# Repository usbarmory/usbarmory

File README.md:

Introduction
============

The USB armory is an open source hardware design, implementing a compact secure
computer.

This repository is aimed towards developers, if you wish to purchase a USB
armory board please see the [ordering information](https://github.com/usbarmory/usbarmory/wiki/Ordering-information).

Authors
=======

Andrea Barisani  
andrea@inversepath.com  

Andrej Rosano  
andrej@inversepath.com  

Daniele Bianco  
daniele@inversepath.com  

Documentation
=============

The main documentation can be found on the
[project wiki](https://github.com/usbarmory/usbarmory/wiki).

Board models
============

* [USB armory Mk II LAN](https://github.com/usbarmory/usbarmory/wiki/Mk-II-LAN)

* [USB armory Mk II](https://github.com/usbarmory/usbarmory/wiki/Mk-II-Introduction)

* USB armory Mk I

License
=======

USB armory | https://github.com/usbarmory/usbarmory  
Copyright (c) The USB armory authors

This is an open hardware design licensed under the terms of the CERN Open
Hardware Licence, see board revisions for applicable versions.

This source is distributed WITHOUT ANY EXPRESS OR IMPLIED WARRANTY, INCLUDING
OF MERCHANTABILITY, SATISFACTORY QUALITY AND FITNESS FOR A PARTICULAR PURPOSE.

Please see LICENSE files in each source subdirectory for applicable conditions.

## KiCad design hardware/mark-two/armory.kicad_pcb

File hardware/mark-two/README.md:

Introduction
============

The USB armory is an open source hardware design, implementing a flash drive
sized computer.

This repository is aimed towards developers, if you wish to purchase a USB
armory board please see the [ordering information](https://github.com/usbarmory/usbarmory/wiki/Ordering-information).

Authors
=======

Andrea Barisani  
andrea@inversepath.com  

Andrej Rosano  
andrej@inversepath.com  

Daniele Bianco  
daniele@inversepath.com  

Documentation
=============

The main documentation can be found on the
[project wiki](https://github.com/usbarmory/usbarmory/wiki).

Revision information
====================

This directory contains the hardware design for the USB armory Mk II rev. δ.

Current schematics and layout files have been designed in KiCad 10.0.8.

PCB Information
===============

6 layers, 0.8mm thickness  
Outer layers 0.5 oz base copper foil  
Inner layers   1 oz base copper foil  
width (X) 65.6 mm, height (Y) 19.5 mm  
Electroless Nickel Immersion Gold (ENIG) surface finish  
Black resist, white component legend

Layers
------

Order and type of copper layers:  
  TOP:         signal, front components  
  SIGNAL 1:    signal  
  GND POWER 1: ground and power plane  
  GND POWER 2: ground and power plane  
  SIGNAL 2:    signal  
  BOTTOM:      signal, back components  

| Layer | Description               |  Thickness (in um)  |
|:-----:|---------------------------|:-------------------:|
|       | LPI mask                  |   15                |
|       | ENIG plating              |   18                |
|   1   | copper                    |   30                |
|       | prepreg, 2 x PP 106       |  121                |
|   2   | copper                    |   17                |
|       | core, FR4 17/17           |  125                |
|   3   | copper                    |   17                |
|       | prepreg, 2 x PP 106       |  116                |
|   4   | copper                    |   17                |
|       | core, FR4 17/17           |  125                |
|   5   | copper                    |   17                |
|       | prepreg, 2 x PP 106       |  121                |
|   6   | copper                    |   30                |
|       | ENIG plating              |   18                |
|       | LPI mask                  |   15                |

Material: Isola PCL370-HR
Total thickness: 0.8 mm

DRC information
---------------

Minimum track width:            0.100 mm  
Minimum via diameter:           0.406 mm  
Outer layer track width:        0.100 mm  
Outer layer isolation distance: 0.100 mm  
Outer layer annular ring:       0.075 mm  
Inner layer track width:        0.100 mm  
Inner layer isolation distance: 0.100 mm  
Inner layer annular ring:       0.075 mm  
Smallest final hole (plated):   0.150 mm

Regulatory compliance & handling
================================

The USB armory board is an open system design, which does not include a
shielded enclosure. This may cause interference to other electrical or
electronic devices in close proximity. In a domestic environment, this product
may cause radio interference in which case the user may be required to take
adequate measures. In addition, this board should not be used near any medical
equipment or RF devices.

The board is sensitive to Electrostatic discharge (ESD). Hold the board only by
its edges. After removing the board from its box, place it on a grounded,
static-free surface.

The board can become hot, like any fan-less design, during continuous high CPU
loads, mind its temperature while handling it.

* [Compliance information](https://github.com/usbarmory/usbarmory/wiki/Compliance-information)

License
=======

USB armory | https://github.com/usbarmory/usbarmory  
Copyright (c) The USB armory authors

This source describes Open Hardware and is licensed under the CERN-OHL-S v2.

You may redistribute and modify this source and make products using it under
the terms of the CERN-OHL-S v2 (https://ohwr.org/cern_ohl_s_v2.txt).

This source is distributed WITHOUT ANY EXPRESS OR IMPLIED WARRANTY, INCLUDING
OF MERCHANTABILITY, SATISFACTORY QUALITY AND FITNESS FOR A PARTICULAR PURPOSE.
Please see the CERN-OHL-S v2 for applicable conditions.

As per CERN-OHL-S v2 section 4, should You produce hardware based on this
source, You must where practicable maintain the Source Location visible on the
external case of the USB armory or other products you make using this source.

The following exceptions apply:

- `../lib.snapeda`: all files in this directory are imported or modified
  from SnapEDA symbols and footprints, therefore the license at
  https://www.snapeda.com/about/FAQ/#license applies.

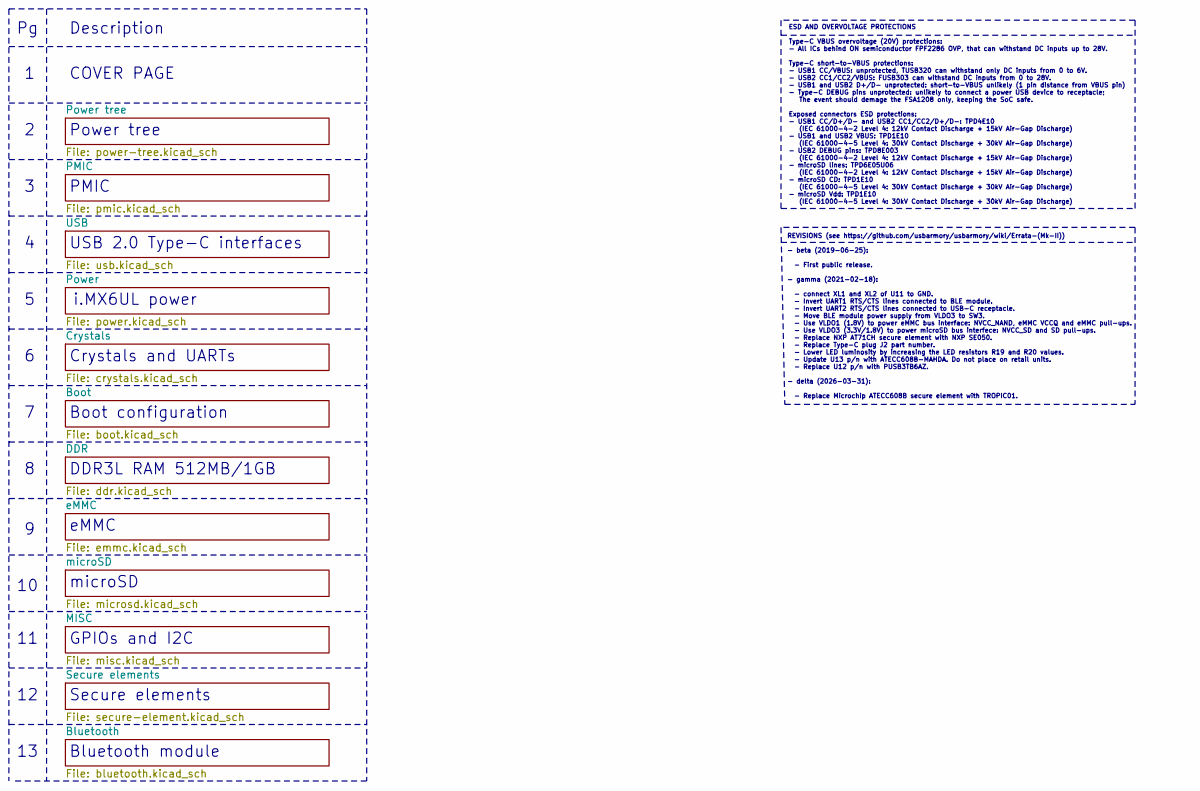
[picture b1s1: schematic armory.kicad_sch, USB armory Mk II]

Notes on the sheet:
Crystals and UARTs
ESD AND OVERVOLTAGE PROTECTIONS Type-C VBUS overvoltage (20V) protections: - All ICs behind ON semiconductor FPF2286 OVP, that can withstand DC inputs up to 28V. Type-C short-to-VBUS protections: - USB1 CC/VBUS: unprotected, TUSB320 can withstand only DC inputs from 0 to 6V. - USB2 CC1/CC2/VBUS: FU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
Power tree
PMIC
Boot configuration
COVER PAGE
microSD
i.MX6UL power
USB 2.0 Type-C interfaces
GPIOs and I2C
eMMC
REVISIONS (see https://github.com/usbarmory/usbarmory/wiki/Errata-(Mk-II)) - beta (2019-06-25): - First public release. - gamma (2021-02-18): - connect XL1 and XL2 of U11 to GND. - Invert UART1 RTS/CTS lines connected to BLE module. - Invert UART2 RTS/CTS lines connected to USB-C receptacle. - Move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
DDR3L RAM 512MB/1GB
Bluetooth module
Description
Secure elements

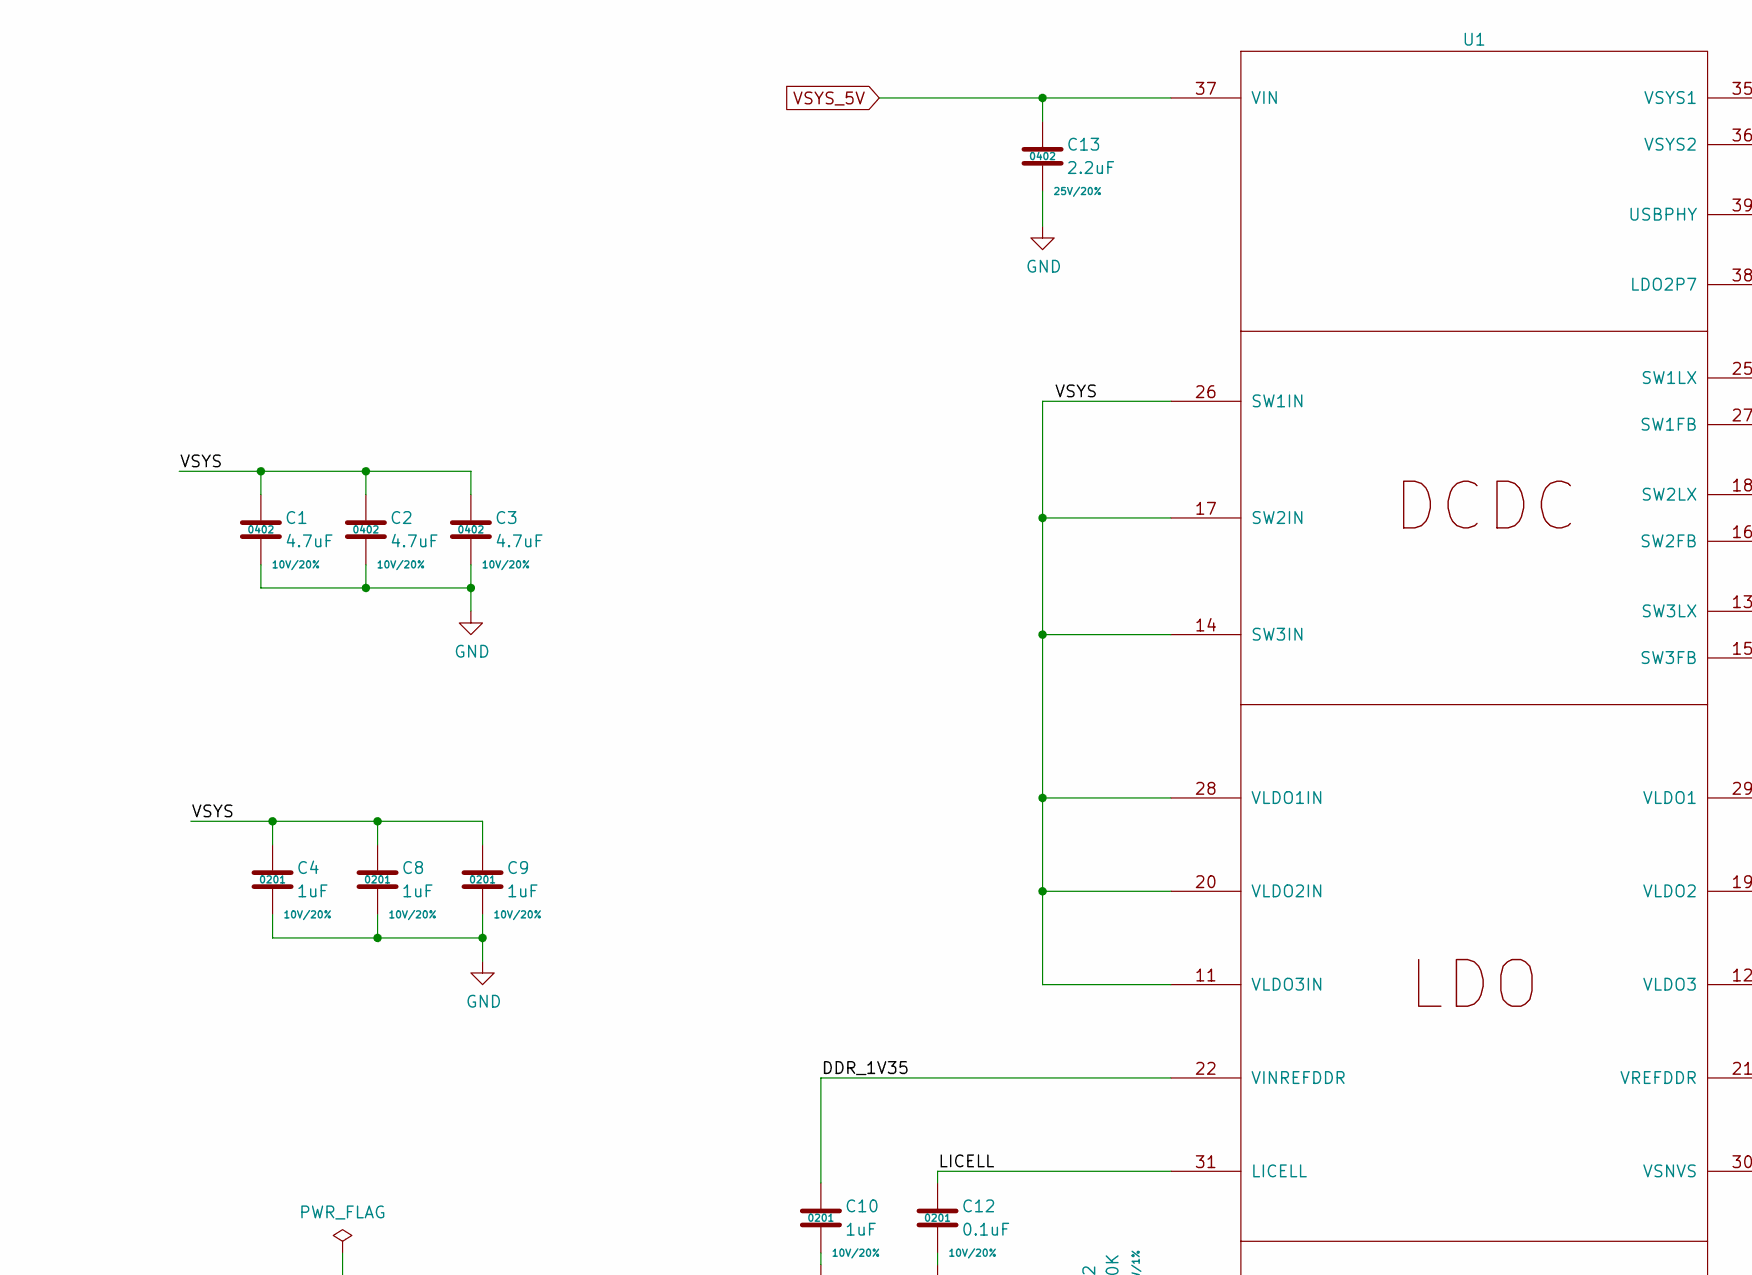
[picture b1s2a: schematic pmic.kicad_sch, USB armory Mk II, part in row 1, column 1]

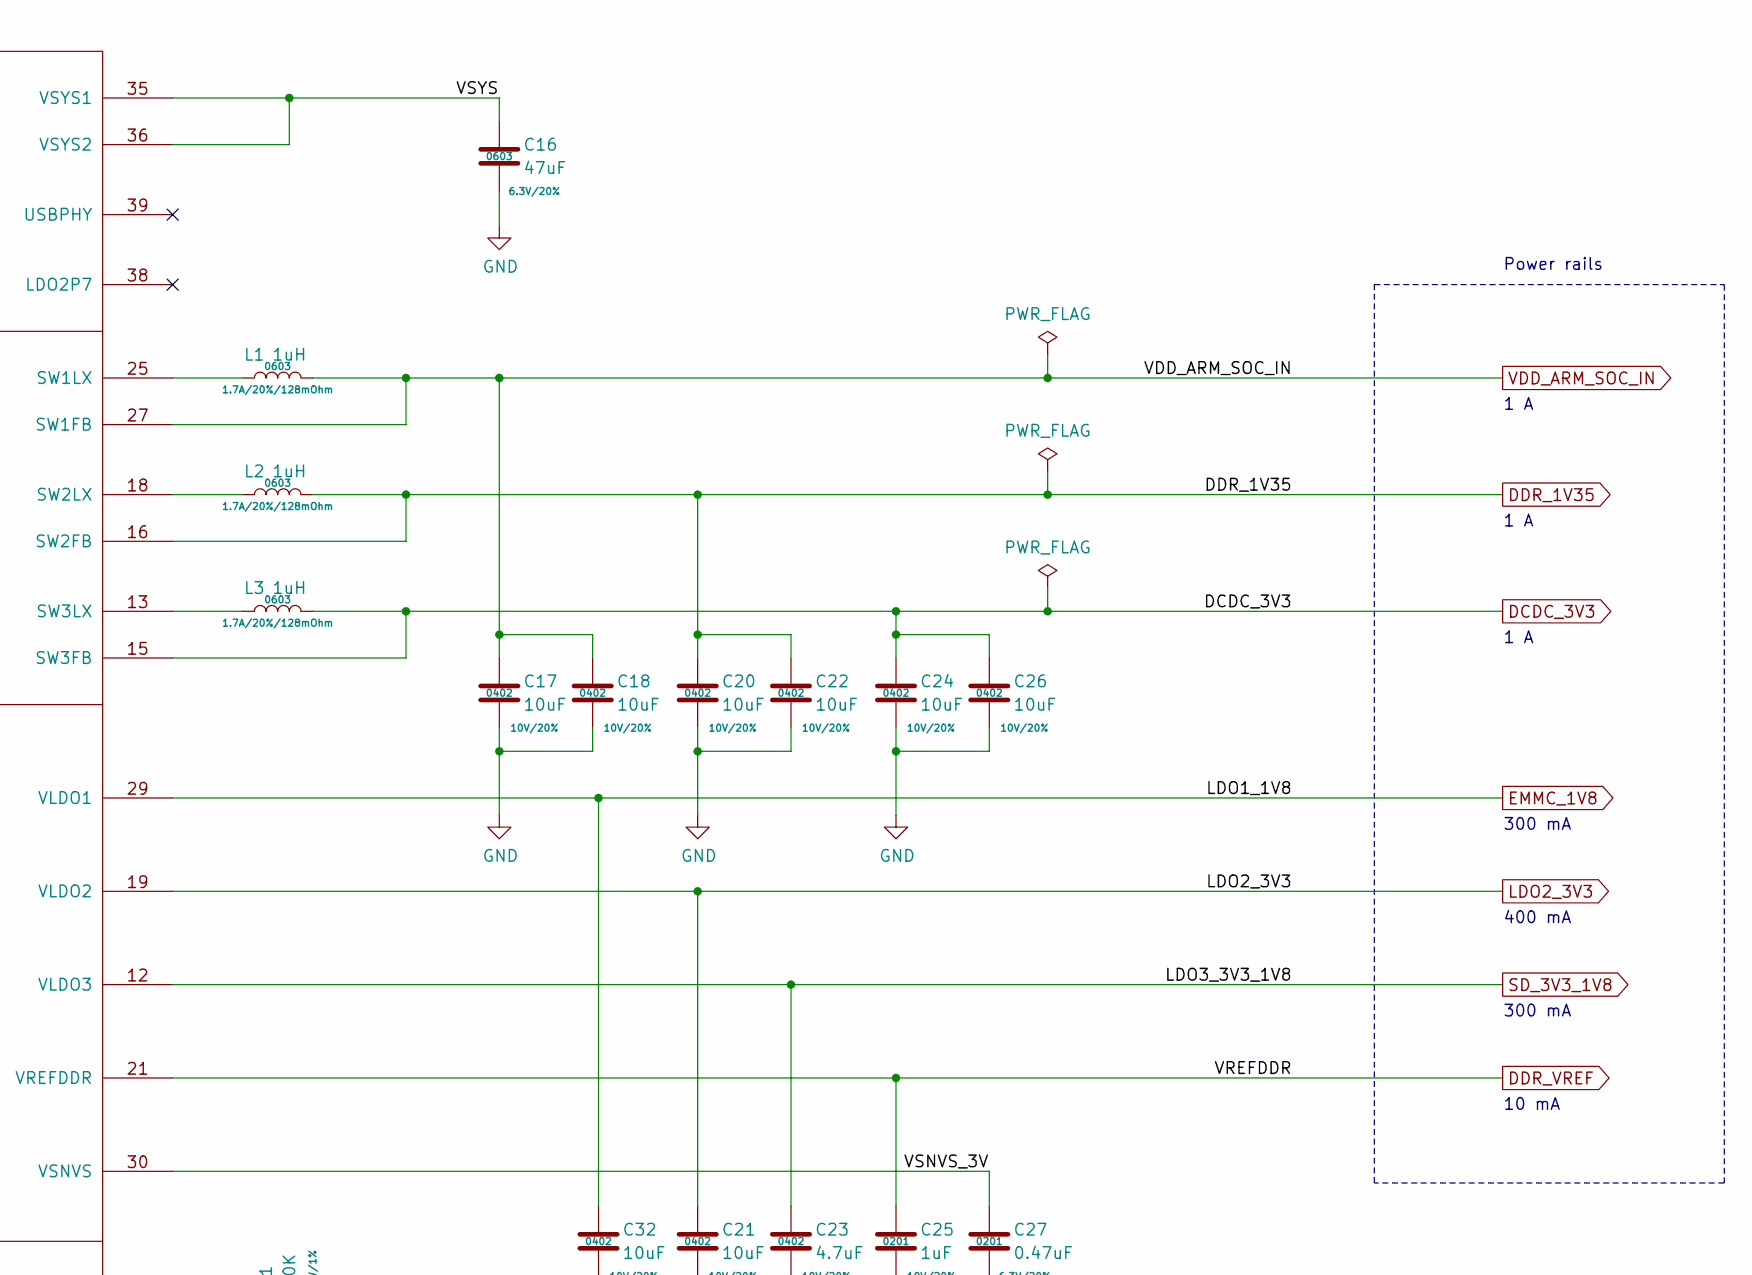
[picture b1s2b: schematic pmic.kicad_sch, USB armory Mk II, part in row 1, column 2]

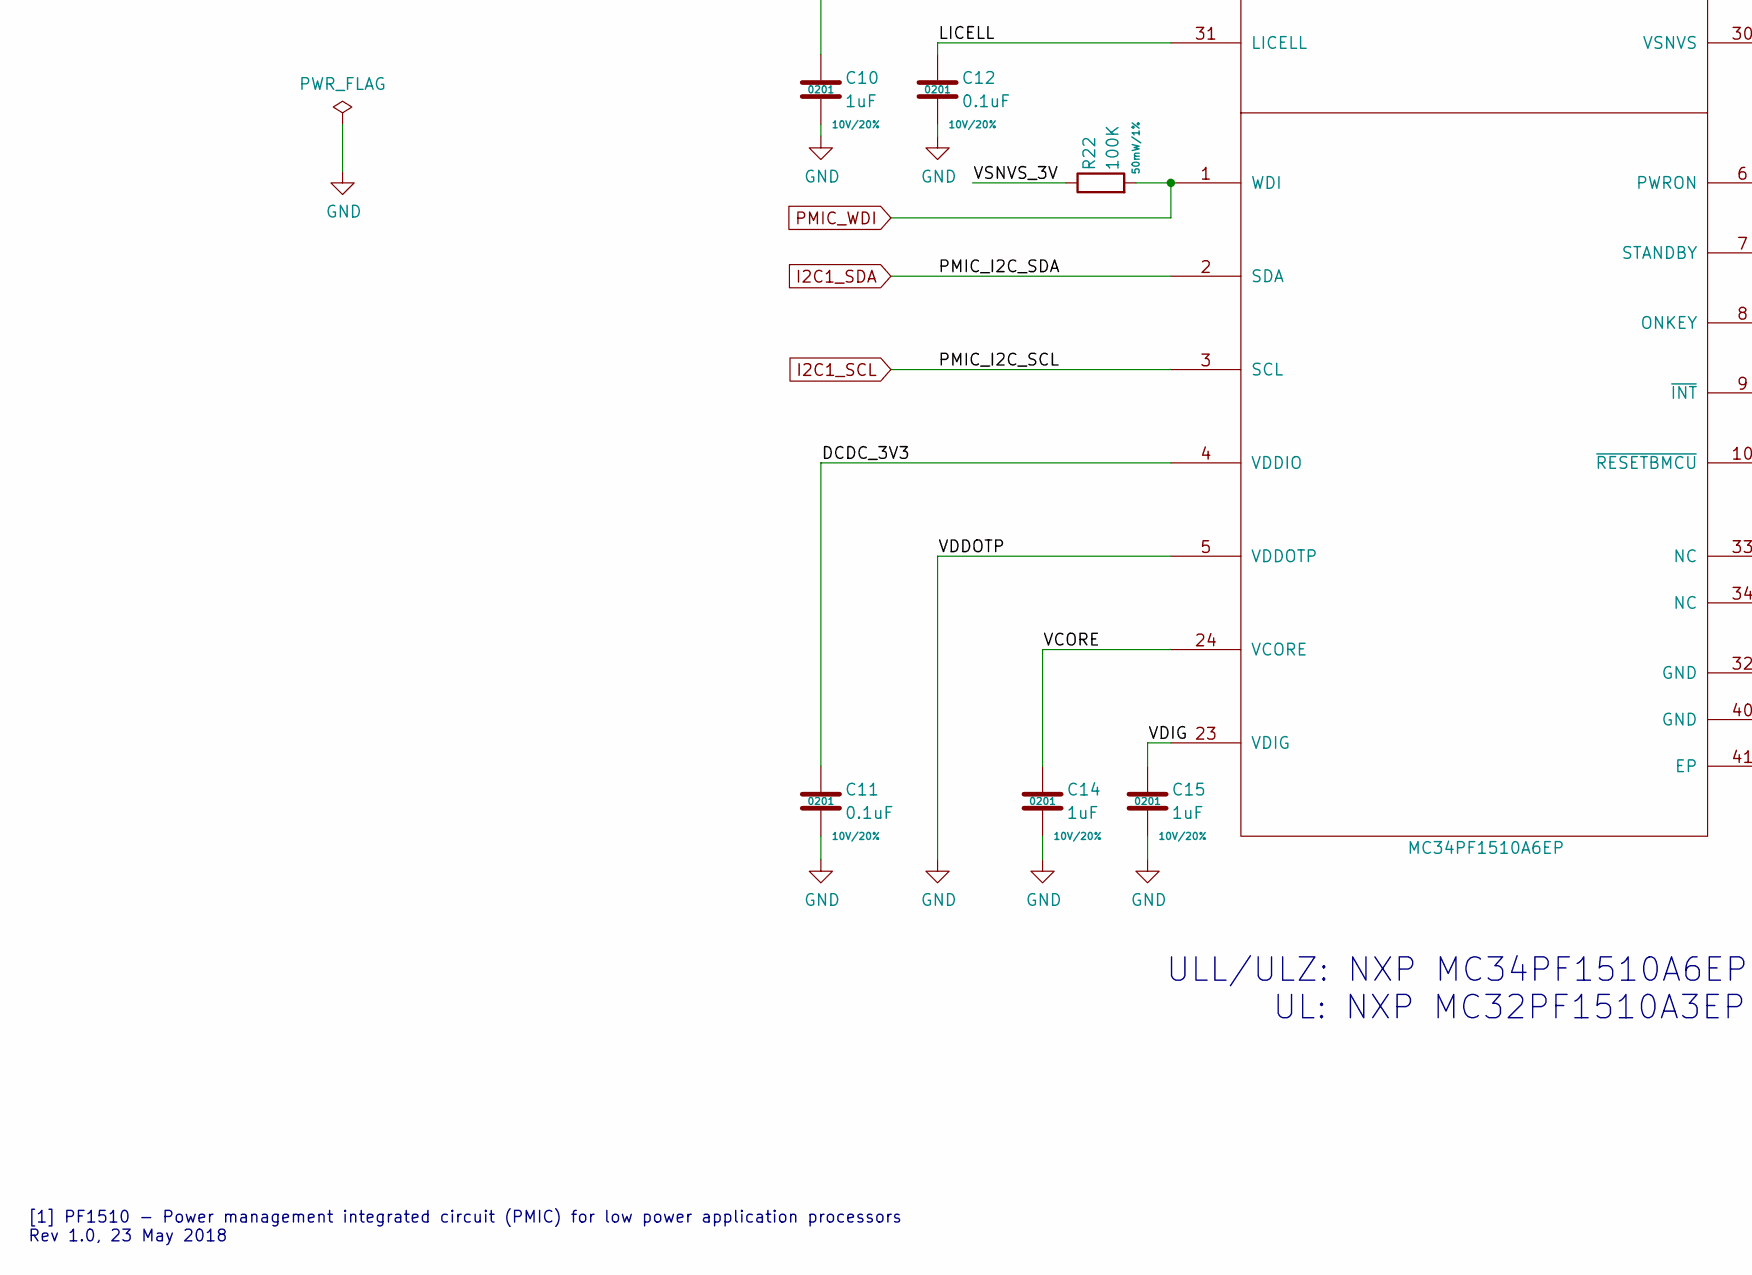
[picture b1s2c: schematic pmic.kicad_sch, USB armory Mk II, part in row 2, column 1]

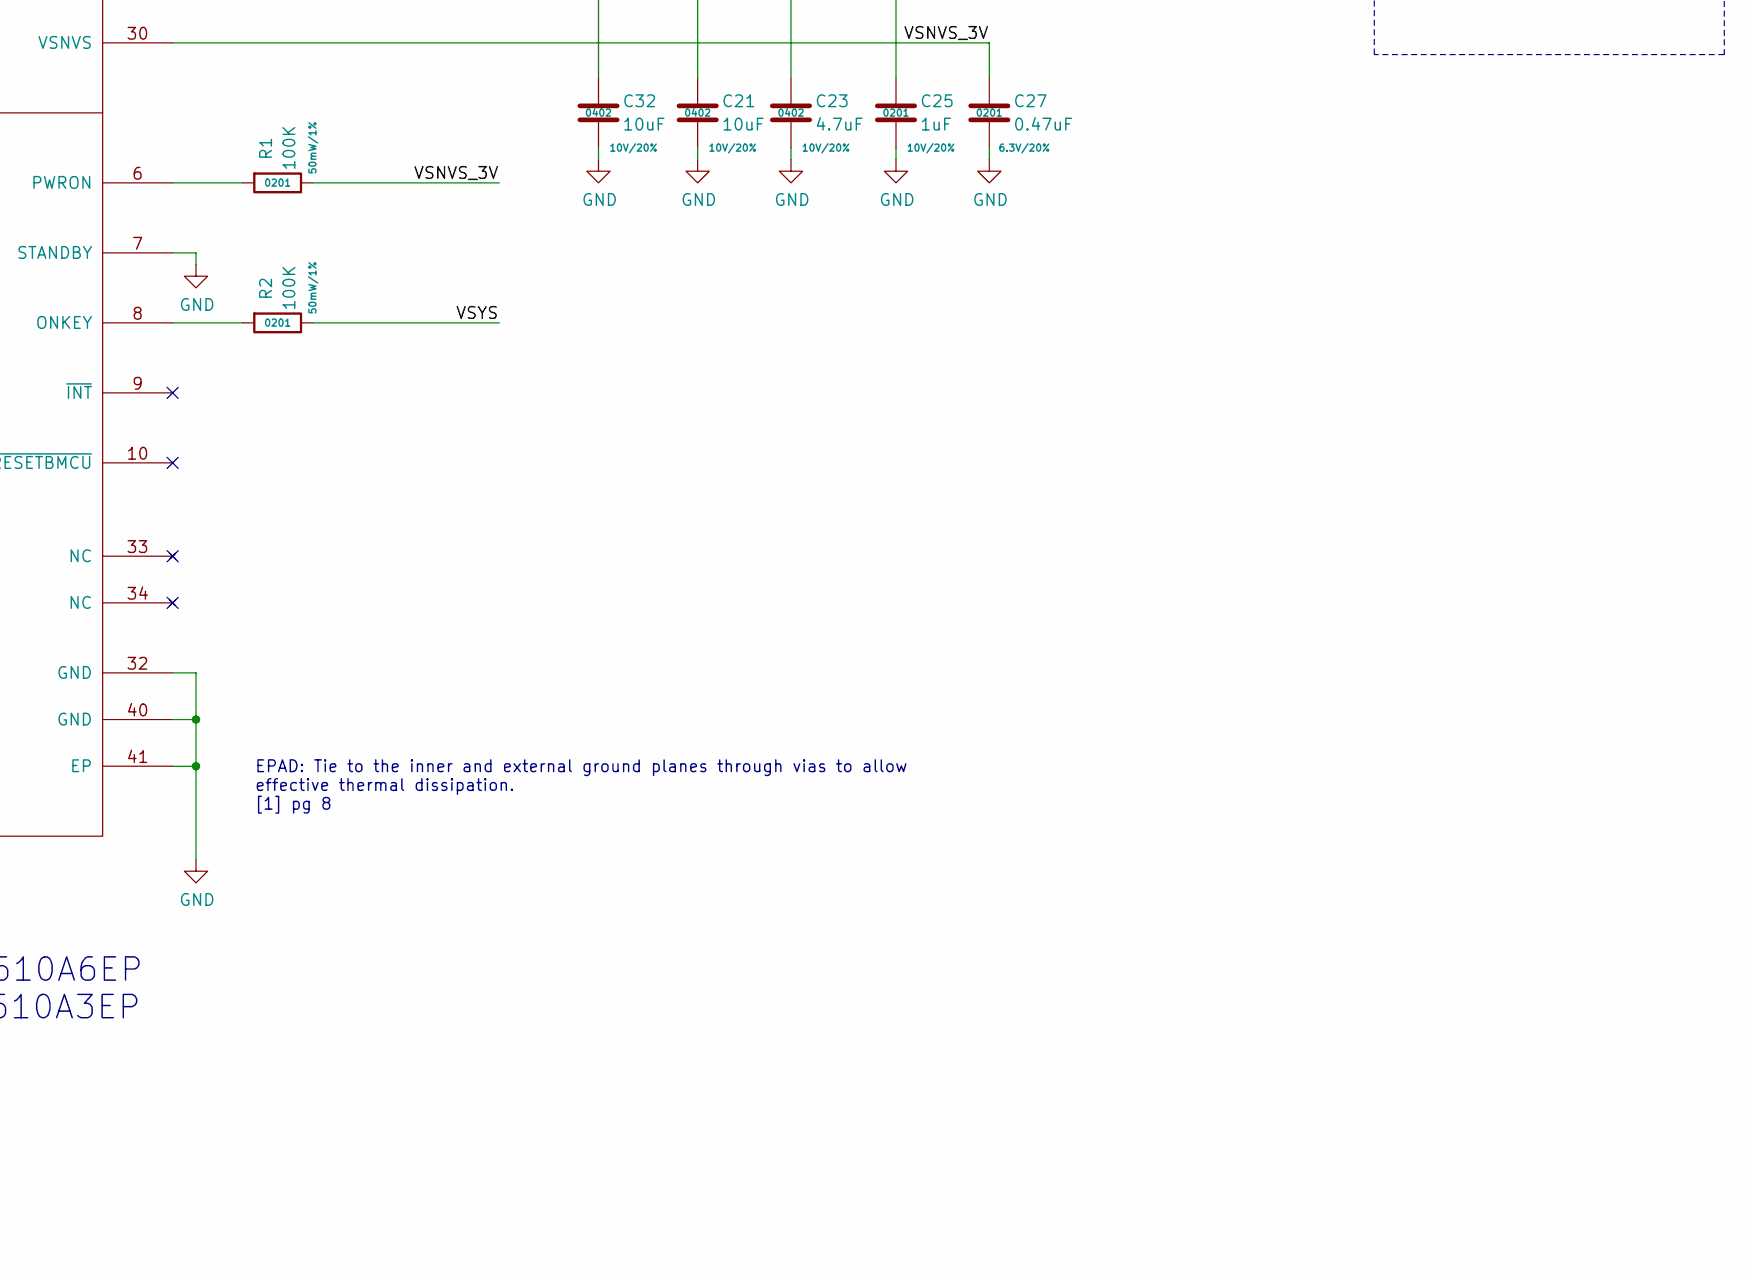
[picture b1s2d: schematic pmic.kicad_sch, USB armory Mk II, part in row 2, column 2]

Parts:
C1, C2, C3, C23: 4.7uF; SM0402; Rating 10V/20%; Mfg PN ZRB15XR61A475ME01D
C4, C8, C9, C10, C14, C15, C25: 1uF; SM0201; Rating 10V/20%; Mfg PN GRM033R61A105ME15D
C11, C12: 0.1uF; SM0201; Rating 10V/20%; Mfg PN GRM033R61A104ME15D
C13: 2.2uF; SM0402; Rating 25V/20%; Mfg PN GRM155R61E225ME15D
C16: 47uF; SM0603; Rating 6.3V/20%; Mfg PN GRM188R60J476ME15D
C17, C18, C20, C21, C22, C24, C26, C32: 10uF; SM0402; Rating 10V/20%; Mfg PN CL05A106MP8NUB8
C27: 0.47uF; SM0201; Rating 6.3V/20%; Mfg PN GRM033R60J474ME90D
L1, L2, L3: 1uH; SM0603; Rating 1.7A/20%/128mOhm; Mfg PN DFE18SAN1R0MG0L
R1, R2, R22: 100K; SM0201; Rating 50mW/1%; Mfg PN CRCW0201100KJNED
U1: MC34PF1510A6EP; SOT1369-4; Mfg PN MC34PF1510A6EP

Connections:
/PMIC/LICELL: C12.1, U1.31 (LICELL)
/PMIC/VCORE: C14.1, U1.24 (VCORE)
/PMIC/VDIG: C15.1, U1.23 (VDIG)
/PMIC/VSNVS_3V: C27.1, R1.1, R22.1, U1.30 (VSNVS)
/PMIC/VSYS: C1.1, C2.1, C3.1, C4.1, C8.1, C9.1, C16.1, R2.1, U1.11 (VLDO3IN), U1.14 (SW3IN), U1.17 (SW2IN), U1.20 (VLDO2IN), U1.26 (SW1IN), U1.28 (VLDO1IN), U1.35 (VSYS1), U1.36 (VSYS2)
DCDC_3V3: C11.1, C24.1, C26.1, L3.2, U1.4 (VDDIO), U1.15 (SW3FB); also elsewhere on the board
DDR_1V35: C10.1, C20.1, C22.1, L2.2, U1.16 (SW2FB), U1.22 (VINREFDDR); also elsewhere on the board
DDR_VREF: C25.1, U1.21 (VREFDDR); also elsewhere on the board
EMMC_1V8: C32.1, U1.29 (VLDO1); also elsewhere on the board
GND: C1.2, C2.2, C3.2, C4.2, C8.2, C9.2, C10.2, C11.2, C12.2, C13.2, C14.2, C15.2, C16.2, C17.2, C18.2, C20.2, C21.2, C22.2, C23.2, C24.2, C25.2, C26.2, C27.2, C32.2, U1.5 (VDDOTP), U1.7 (STANDBY), U1.32 (GND), U1.40 (GND), U1.41 (EP); also elsewhere on the board
I2C1_SCL: U1.3 (SCL); also elsewhere on the board
I2C1_SDA: U1.2 (SDA); also elsewhere on the board
LDO2_3V3: C21.1, U1.19 (VLDO2); also elsewhere on the board
unnamed: R2.2, U1.8 (ONKEY)
unnamed: R1.2, U1.6 (PWRON)
unnamed: L1.1, U1.25 (SW1LX)
unnamed: L2.1, U1.18 (SW2LX)
unnamed: L3.1, U1.13 (SW3LX)
PMIC_WDI: R22.2, U1.1 (WDI); also elsewhere on the board
SD_3V3_1V8: C23.1, U1.12 (VLDO3); also elsewhere on the board
VDD_ARM_SOC_IN: C17.1, C18.1, L1.2, U1.27 (SW1FB); also elsewhere on the board
VSYS_5V: C13.1, U1.37 (VIN); also elsewhere on the board

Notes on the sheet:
300 mA
EPAD: Tie to the inner and external ground planes through vias to allow effective thermal dissipation. [1] pg 8
10 mA
ULL/ULZ: NXP MC34PF1510A6EP UL: NXP MC32PF1510A3EP
1 A
[1] PF1510 - Power management integrated circuit (PMIC) for low power application processors Rev 1.0, 23 May 2018
Power rails
400 mA

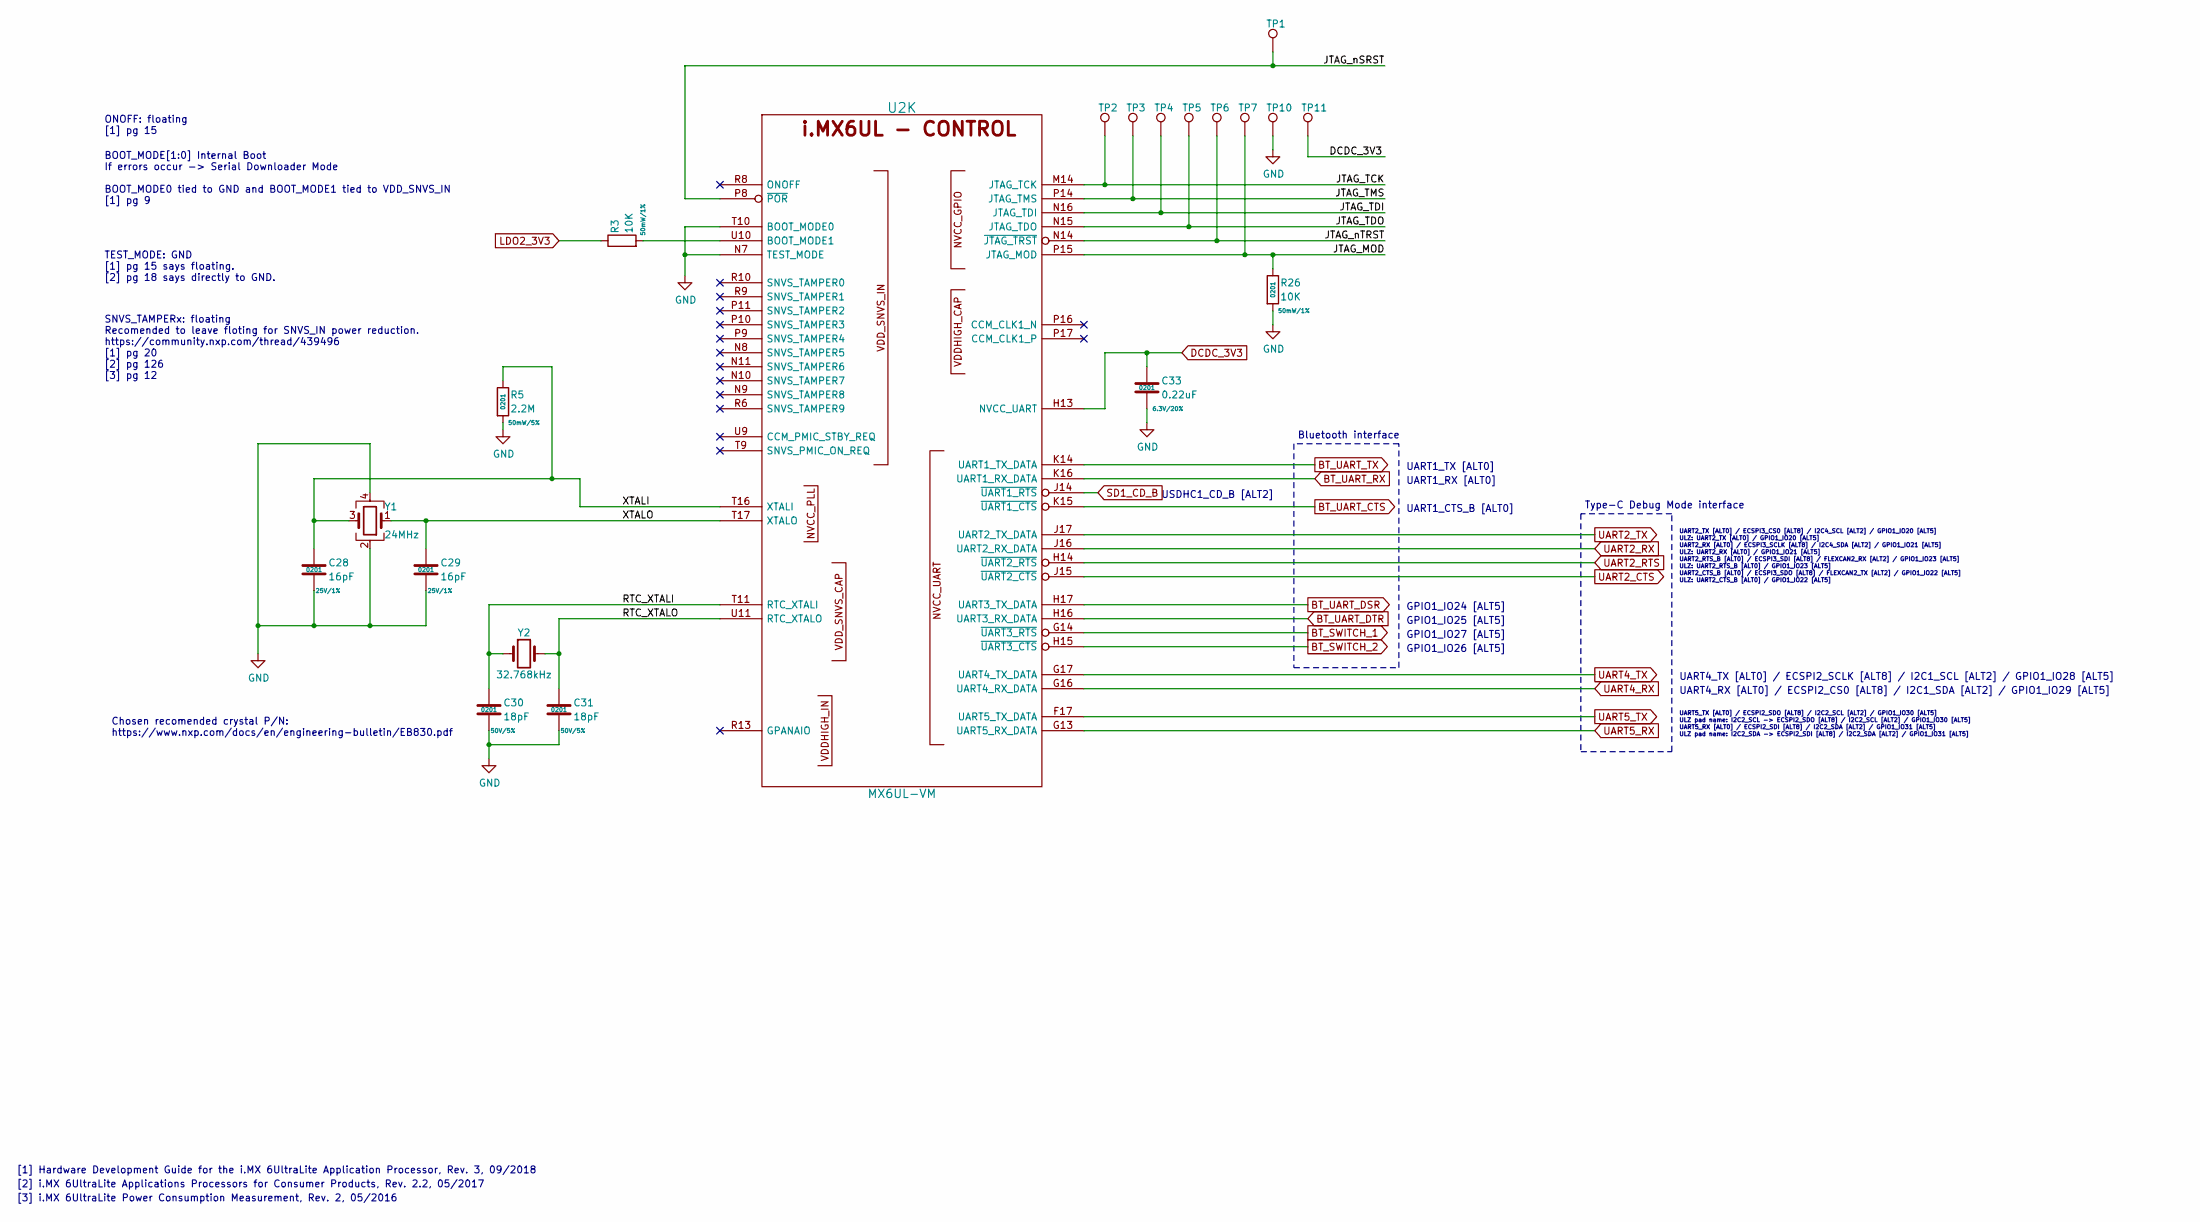
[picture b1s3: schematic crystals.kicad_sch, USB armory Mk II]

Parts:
C28, C29: 16pF; SM0201; Rating 25V/1%; Mfg PN CBR02C160F3GAC
C30, C31: 18pF; SM0201; Rating 50V/5%; Mfg PN GRM0335C1H180JA01D
C33: 0.22uF; SM0201; Rating 6.3V/20%; Mfg PN GRM033R60J224ME15D
R3, R26: 10K; SM0201; Rating 50mW/1%; Mfg PN CRCW020110K0JNED
R5: 2.2M; SM0201; Rating 50mW/5%; Mfg PN RC0201JR-072M2L
TP1, TP2, TP3, TP4, TP5, TP6, TP7, TP10, TP11: TestPoint; TP
U2: MX6UL-VM; SOT1534-2; Mfg PN MCIMX6Z0DVM09AB
Y1: 24MHz; TSX-3225; Mfg PN TSX-3225 24.0000MF15X-AC3
Y2: 32.768kHz; CM7V-T1A; Mfg PN CM7V-T1A-32.768kHz-12.5pF-20PPM-TA-QC

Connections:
/Crystals/JTAG_MOD: R26.1, TP7.1 (1_1), U2.P15 (JTAG_MOD)
/Crystals/JTAG_TCK: TP2.1 (1_1), U2.M14 (JTAG_TCK)
/Crystals/JTAG_TDI: TP4.1 (1_1), U2.N16 (JTAG_TDI)
/Crystals/JTAG_TDO: TP5.1 (1_1), U2.N15 (JTAG_TDO)
/Crystals/JTAG_TMS: TP3.1 (1_1), U2.P14 (JTAG_TMS)
/Crystals/JTAG_nSRST: TP1.1 (1_1), U2.P8 (~POR)
/Crystals/JTAG_nTRST: TP6.1 (1_1), U2.N14 (~JTAG_TRST)
/Crystals/RTC_XTALI: C30.1, U2.T11 (RTC_XTALI), Y2.1
/Crystals/RTC_XTALO: C31.1, U2.U11 (RTC_XTALO), Y2.2
/Crystals/XTALI: C28.1, R5.1, U2.T16 (XTALI), Y1.3
/Crystals/XTALO: C29.1, U2.T17 (XTALO), Y1.1
BT_SWITCH_1: U2.G14 (~UART3_RTS); also elsewhere on the board
BT_SWITCH_2: U2.H15 (~UART3_CTS); also elsewhere on the board
BT_UART_CTS: U2.K15 (~UART1_CTS); also elsewhere on the board
BT_UART_DSR: U2.H17 (UART3_TX_DATA); also elsewhere on the board
BT_UART_DTR: U2.H16 (UART3_RX_DATA); also elsewhere on the board
BT_UART_RX: U2.K16 (UART1_RX_DATA); also elsewhere on the board
BT_UART_TX: U2.K14 (UART1_TX_DATA); also elsewhere on the board
DCDC_3V3: C33.1, TP11.1 (1_1), U2.H13 (NVCC_UART); also elsewhere on the board
GND: C28.2, C29.2, C30.2, C31.2, C33.2, R5.2, R26.2, TP10.1 (1_1), U2.N7 (TEST_MODE), U2.T10 (BOOT_MODE0), Y1.2, Y1.4; also elsewhere on the board
LDO2_3V3: R3.1; also elsewhere on the board
unnamed: R3.2, U2.U10 (BOOT_MODE1)
SD1_CD_B: U2.J14 (~UART1_RTS); also elsewhere on the board
UART2_CTS: U2.J15 (~UART2_CTS); also elsewhere on the board
UART2_RTS: U2.H14 (~UART2_RTS); also elsewhere on the board
UART2_RX: U2.J16 (UART2_RX_DATA); also elsewhere on the board
UART2_TX: U2.J17 (UART2_TX_DATA); also elsewhere on the board
UART4_RX: U2.G16 (UART4_RX_DATA); also elsewhere on the board
UART4_TX: U2.G17 (UART4_TX_DATA); also elsewhere on the board
UART5_RX: U2.G13 (UART5_RX_DATA); also elsewhere on the board
UART5_TX: U2.F17 (UART5_TX_DATA); also elsewhere on the board

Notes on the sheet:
UART1_RX [ALT0]
UART4_RX [ALT0] / ECSPI2_CS0 [ALT8] / I2C1_SDA [ALT2] / GPIO1_IO29 [ALT5]
UART4_TX [ALT0] / ECSPI2_SCLK [ALT8] / I2C1_SCL [ALT2] / GPIO1_IO28 [ALT5]
BOOT_MODE[1:0] Internal Boot If errors occur -> Serial Downloader Mode BOOT_MODE0 tied to GND and BOOT_MODE1 tied to VDD_SNVS_IN [1] pg 9
GPIO1_IO26 [ALT5]
UART2_RX [ALT0] / ECSPI3_SCLK [ALT8] / I2C4_SDA [ALT2] / GPIO1_IO21 [ALT5]
UART5_RX [ALT0] / ECSPI2_SDI [ALT8] / I2C2_SDA [ALT2] / GPIO1_IO31 [ALT5]
ULZ: UART2_RX [ALT0] / GPIO1_IO21 [ALT5]
GPIO1_IO25 [ALT5]
UART5_TX [ALT0] / ECSPI2_SDO [ALT8] / I2C2_SCL [ALT2] / GPIO1_IO30 [ALT5]
GPIO1_IO24 [ALT5]
ULZ: UART2_CTS_B [ALT0] / GPIO1_IO22 [ALT5]
USDHC1_CD_B [ALT2]
[3] i.MX 6UltraLite Power Consumption Measurement, Rev. 2, 05/2016
Chosen recomended crystal P/N: https://www.nxp.com/docs/en/engineering-bulletin/EB830.pdf
UART2_TX [ALT0] / ECSPI3_CS0 [ALT8] / I2C4_SCL [ALT2] / GPIO1_IO20 [ALT5]
ULZ pad name: I2C2_SCL -> ECSPI2_SDO [ALT8] / I2C2_SCL [ALT2] / GPIO1_IO30 [ALT5]
ULZ: UART2_TX [ALT0] / GPIO1_IO20 [ALT5]
ONOFF: floating [1] pg 15
ULZ pad name: I2C2_SDA -> ECSPI2_SDI [ALT8] / I2C2_SDA [ALT2] / GPIO1_IO31 [ALT5]
UART2_CTS_B [ALT0] / ECSPI3_SDO [ALT8] / FLEXCAN2_TX [ALT2] / GPIO1_IO22 [ALT5]
UART1_CTS_B [ALT0]
SNVS_TAMPERx: floating Recomended to leave floting for SNVS_IN power reduction. https://community.nxp.com/thread/439496 [1] pg 20 [2] pg 126 [3] pg 12
[1] Hardware Development Guide for the i.MX 6UltraLite Application Processor, Rev. 3, 09/2018
Type-C Debug Mode interface
[2] i.MX 6UltraLite Applications Processors for Consumer Products, Rev. 2.2, 05/2017
GPIO1_IO27 [ALT5]
UART2_RTS_B [ALT0] / ECSPI3_SDI [ALT8] / FLEXCAN2_RX [ALT2] / GPIO1_IO23 [ALT5]
Bluetooth interface
TEST_MODE: GND [1] pg 15 says floating. [2] pg 18 says directly to GND.
ULZ: UART2_RTS_B [ALT0] / GPIO1_IO23 [ALT5]
UART1_TX [ALT0]

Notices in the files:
armory-alpha/USB.sch:
Copyright © 2014 Inverse Path S.r.l.
License: GNU General Public License, version 2
hardware/alpha/RAM.sch:
License: CERN OHL v1.2
hardware/mark-two-lan/armory.kicad_sch:
License: CERN-OHL-S
